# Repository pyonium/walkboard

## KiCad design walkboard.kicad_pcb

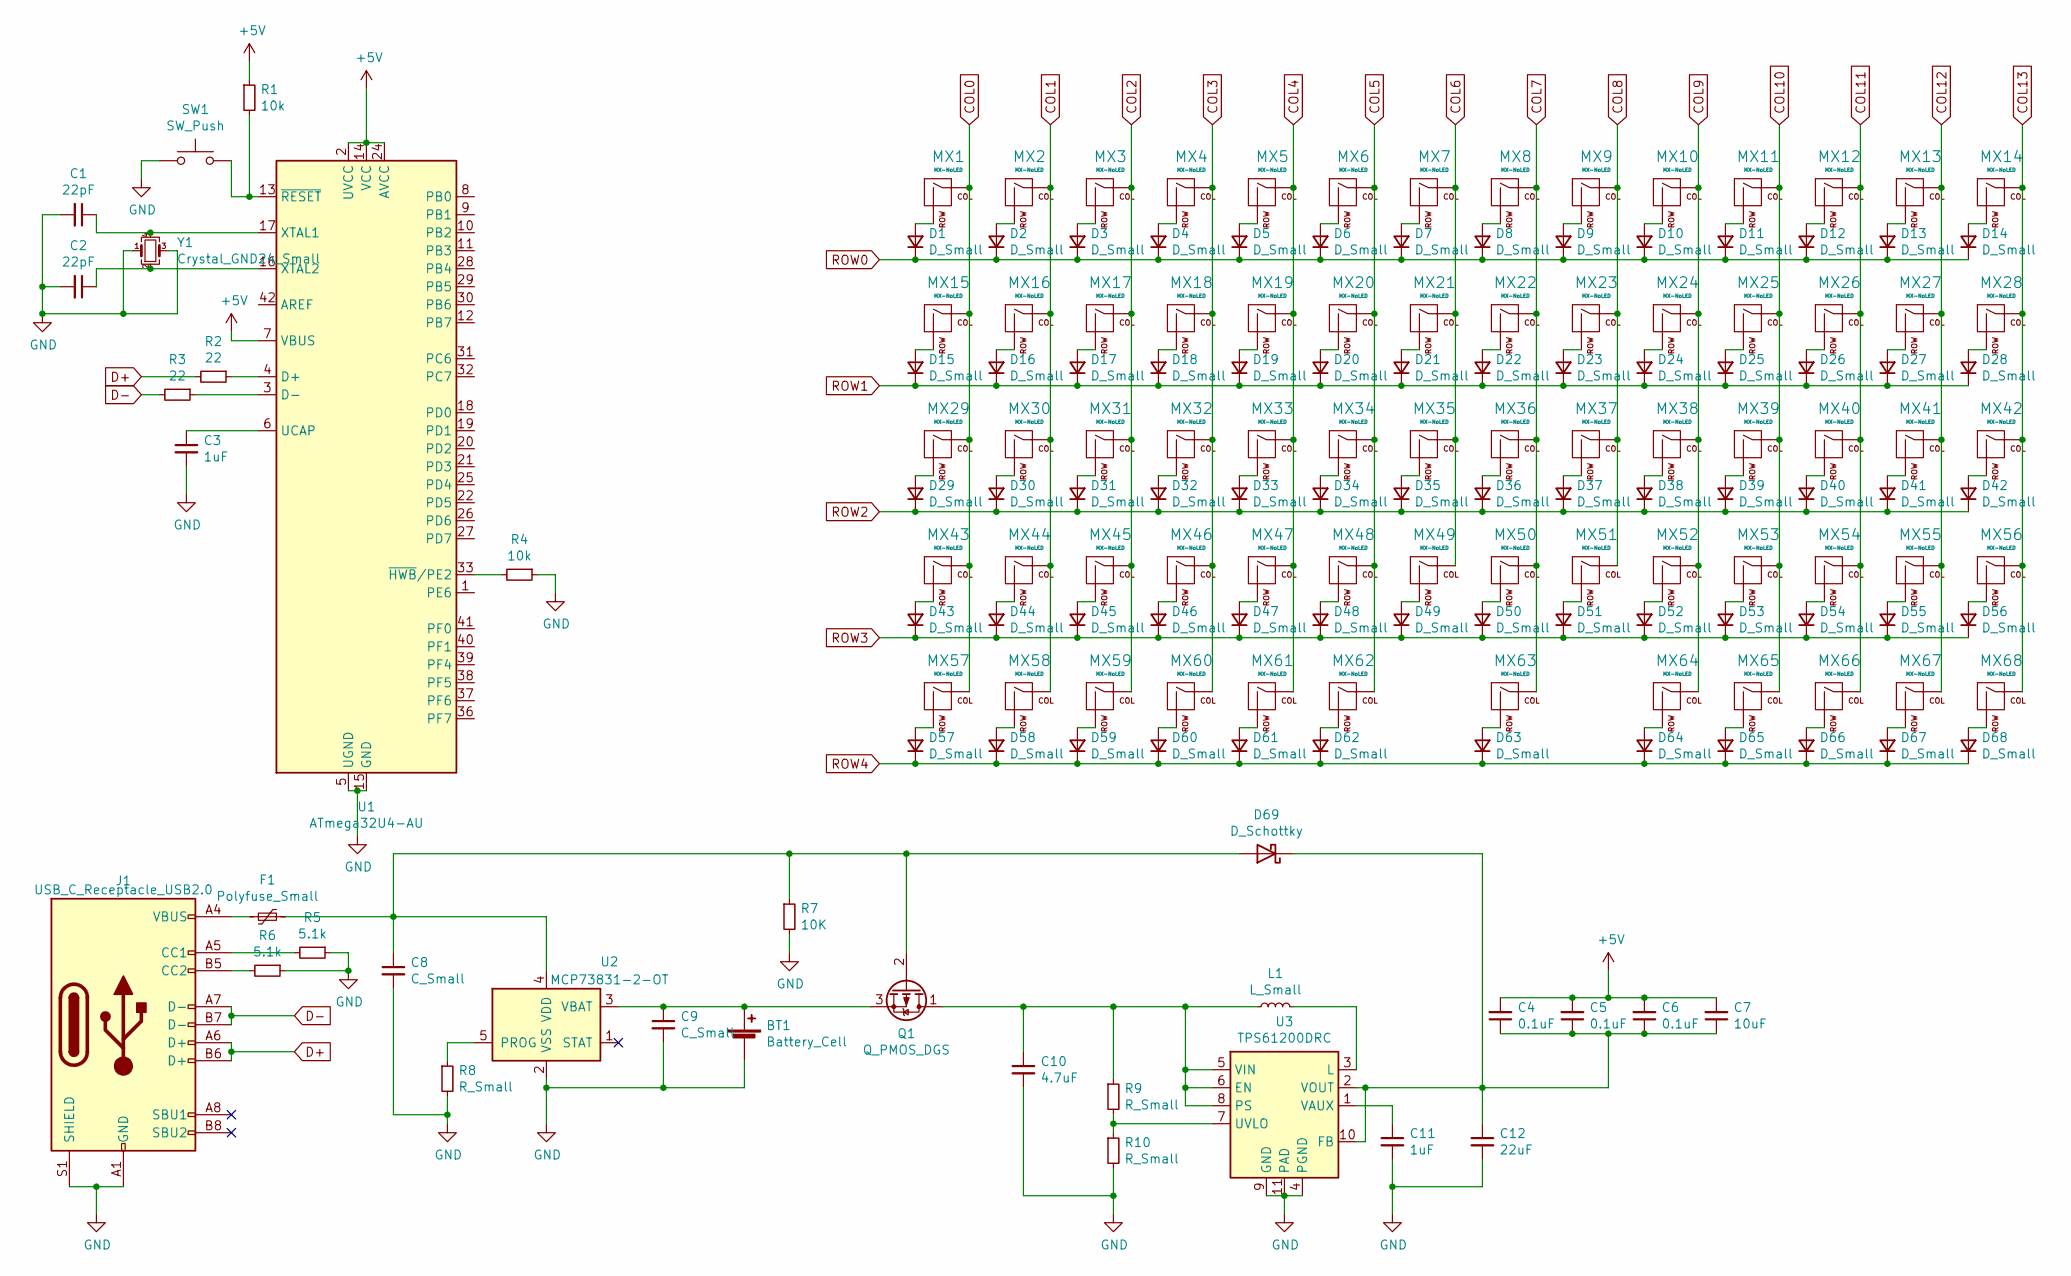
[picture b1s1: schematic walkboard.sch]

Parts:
BT1: Battery_Cell; JST_XH_S2B-XH-A_1x02_P2.50mm_Horizontal
C1, C2: 22pF; C_0805_2012Metric_Pad1.15x1.40mm_HandSolder
C3, C11: 1uF; C_0805_2012Metric_Pad1.15x1.40mm_HandSolder
C4, C5, C6: 0.1uF; C_0805_2012Metric_Pad1.15x1.40mm_HandSolder
C7: 10uF; C_0805_2012Metric_Pad1.15x1.40mm_HandSolder
C8, C9: C_Small; C_0805_2012Metric_Pad1.15x1.40mm_HandSolder
C10: 4.7uF; C_0805_2012Metric_Pad1.15x1.40mm_HandSolder
C12: 22uF; C_0805_2012Metric_Pad1.15x1.40mm_HandSolder
D1, D2, D3, D4, D5, D6, D7, D8, D9, D10, D11, D12, D13, D14, D15, D16, D17, D18, D19, D20, D21, D22, D23, D24, D25, D26, D27, D28, D29, D30, D31, D32, D33, D34, D35, D36, D37, D38, D39, D40, D41, D42, D43, D44, D45, D46, D47, D48, D49, D50, D51, D52, D53, D54, D55, D56, D57, D58, D59, D60, D61, D62, D63, D64, D65, D66, D67, D68: D_Small; D_SOD-123
D69: D_Schottky; D_SOD-123
F1: Polyfuse_Small; Fuse_1206_3216Metric_Pad1.42x1.75mm_HandSolder
J1: USB_C_Receptacle_USB2.0; USB_C_Receptacle_HRO_TYPE-C-31-M-12
L1: L_Small; L_0805_2012Metric_Pad1.15x1.40mm_HandSolder
MX1, MX2, MX3, MX4, MX5, MX6, MX7, MX8, MX9, MX10, MX11, MX12, MX13, MX14, MX15, MX16, MX17, MX18, MX19, MX20, MX21, MX22, MX23, MX24, MX25, MX26, MX27, MX28, MX29, MX30, MX31, MX32, MX33, MX34, MX35, MX36, MX37, MX38, MX39, MX40, MX41, MX42, MX43, MX44, MX45, MX46, MX47, MX48, MX49, MX50, MX51, MX52, MX53, MX54, MX55, MX56, MX57, MX58, MX59, MX60, MX61, MX62, MX63, MX64, MX65, MX66, MX67, MX68: MX-NoLED; Kailh_socket_MX
Q1: Q_PMOS_DGS; SOT-23
R1, R4: 10k; R_0805_2012Metric_Pad1.15x1.40mm_HandSolder
R2, R3: 22; R_0805_2012Metric_Pad1.15x1.40mm_HandSolder
R5, R6: 5.1k; R_0805_2012Metric_Pad1.15x1.40mm_HandSolder
R7: 10K; R_0805_2012Metric_Pad1.15x1.40mm_HandSolder
R8, R9, R10: R_Small; R_0805_2012Metric_Pad1.15x1.40mm_HandSolder
SW1: SW_Push; SKQG-1155865
U1: ATmega32U4-AU; TQFP-44_10x10mm_P0.8mm
U2: MCP73831-2-OT; SOT-23-5
U3: TPS61200DRC; Texas_S-PVSON-N10_ThermalVias
Y1: Crystal_GND24_Small; Crystal_SMD_3225-4Pin_3.2x2.5mm

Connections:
+5V: C4.2, C5.2, C6.2, C7.2, R1.1, U1.2 (UVCC), U1.7 (VBUS), U1.14 (VCC), U1.24 (AVCC), U1.34 (VCC), U1.44 (AVCC)
COL0: MX1.1 (COL), MX15.1 (COL), MX29.1 (COL), MX43.1 (COL), MX57.1 (COL)
COL1: MX2.1 (COL), MX16.1 (COL), MX30.1 (COL), MX44.1 (COL), MX58.1 (COL)
COL2: MX3.1 (COL), MX17.1 (COL), MX31.1 (COL), MX45.1 (COL), MX59.1 (COL)
COL3: MX4.1 (COL), MX18.1 (COL), MX32.1 (COL), MX46.1 (COL), MX60.1 (COL)
COL4: MX5.1 (COL), MX19.1 (COL), MX33.1 (COL), MX47.1 (COL), MX61.1 (COL)
COL5: MX6.1 (COL), MX20.1 (COL), MX34.1 (COL), MX48.1 (COL), MX62.1 (COL)
COL6: MX7.1 (COL), MX21.1 (COL), MX35.1 (COL), MX49.1 (COL)
COL7: MX8.1 (COL), MX22.1 (COL), MX36.1 (COL), MX50.1 (COL), MX63.1 (COL)
COL8: MX9.1 (COL), MX23.1 (COL), MX37.1 (COL), MX51.1 (COL)
COL9: MX10.1 (COL), MX24.1 (COL), MX38.1 (COL), MX52.1 (COL), MX64.1 (COL)
COL10: MX11.1 (COL), MX25.1 (COL), MX39.1 (COL), MX53.1 (COL), MX65.1 (COL)
COL11: MX12.1 (COL), MX26.1 (COL), MX40.1 (COL), MX54.1 (COL), MX66.1 (COL)
COL12: MX13.1 (COL), MX27.1 (COL), MX41.1 (COL), MX55.1 (COL), MX67.1 (COL)
COL13: MX14.1 (COL), MX28.1 (COL), MX42.1 (COL), MX56.1 (COL), MX68.1 (COL)
D+: J1.A6 (D+), J1.B6 (D+), R2.2
D-: J1.A7 (D-), J1.B7 (D-), R3.2
GND: BT1.2 (-), C1.2, C2.2, C3.2, C8.2, C9.2, C10.2, C11.2, C12.2, J1.A1 (GND), J1.A12 (GND), J1.B1 (GND), J1.B12 (GND), J1.S1 (SHIELD), R4.1, R5.1, R6.1, R7.2, R8.2, R10.2, SW1.1, U1.5 (UGND), U1.15 (GND), U1.23 (GND), U1.35 (GND), U1.43 (GND), U2.2 (VSS), U3.4 (PGND), U3.9 (GND), U3.11 (PAD), Y1.1, Y1.3
unnamed: BT1.1 (+), C9.1, Q1.3 (S), U2.3 (VBAT)
unnamed: C1.1, U1.17 (XTAL1), Y1.4
unnamed: C2.1, U1.16 (XTAL2), Y1.2
unnamed: C3.1, U1.6 (UCAP)
unnamed: C8.1, D69.2 (A), F1.2, Q1.2 (G), R7.1, U2.4 (VDD)
unnamed: C10.1, L1.1, Q1.1 (D), R9.1, U3.5 (VIN), U3.6 (EN), U3.8 (PS)
unnamed: C11.1, U3.1 (VAUX)
unnamed: C4.1, C5.1, C6.1, C7.1, C12.1, D69.1 (K), U3.2 (VOUT), U3.10 (FB)
unnamed: D1.2 (A), MX1.2 (ROW)
unnamed: D2.2 (A), MX2.2 (ROW)
unnamed: D3.2 (A), MX3.2 (ROW)
unnamed: D4.2 (A), MX4.2 (ROW)
unnamed: D5.2 (A), MX5.2 (ROW)
unnamed: D6.2 (A), MX6.2 (ROW)
unnamed: D7.2 (A), MX7.2 (ROW)
unnamed: D8.2 (A), MX8.2 (ROW)
unnamed: D9.2 (A), MX9.2 (ROW)
unnamed: D10.2 (A), MX10.2 (ROW)
unnamed: D11.2 (A), MX11.2 (ROW)
unnamed: D12.2 (A), MX12.2 (ROW)
unnamed: D13.2 (A), MX13.2 (ROW)
unnamed: D14.2 (A), MX14.2 (ROW)
unnamed: D15.2 (A), MX15.2 (ROW)
unnamed: D16.2 (A), MX16.2 (ROW)
unnamed: D17.2 (A), MX17.2 (ROW)
unnamed: D18.2 (A), MX18.2 (ROW)
unnamed: D19.2 (A), MX19.2 (ROW)
unnamed: D20.2 (A), MX20.2 (ROW)
unnamed: D21.2 (A), MX21.2 (ROW)
unnamed: D22.2 (A), MX22.2 (ROW)
unnamed: D23.2 (A), MX23.2 (ROW)
unnamed: D24.2 (A), MX24.2 (ROW)
unnamed: D25.2 (A), MX25.2 (ROW)
unnamed: D26.2 (A), MX26.2 (ROW)
unnamed: D27.2 (A), MX27.2 (ROW)
unnamed: D28.2 (A), MX28.2 (ROW)
unnamed: D29.2 (A), MX29.2 (ROW)
unnamed: D30.2 (A), MX30.2 (ROW)
unnamed: D31.2 (A), MX31.2 (ROW)
unnamed: D32.2 (A), MX32.2 (ROW)
unnamed: D33.2 (A), MX33.2 (ROW)
unnamed: D34.2 (A), MX34.2 (ROW)
unnamed: D35.2 (A), MX35.2 (ROW)
unnamed: D36.2 (A), MX36.2 (ROW)
unnamed: D37.2 (A), MX37.2 (ROW)
unnamed: D38.2 (A), MX38.2 (ROW)
unnamed: D39.2 (A), MX39.2 (ROW)
unnamed: D40.2 (A), MX40.2 (ROW)
unnamed: D41.2 (A), MX41.2 (ROW)
unnamed: D42.2 (A), MX42.2 (ROW)
unnamed: D43.2 (A), MX43.2 (ROW)
unnamed: D44.2 (A), MX44.2 (ROW)
unnamed: D45.2 (A), MX45.2 (ROW)
unnamed: D46.2 (A), MX46.2 (ROW)
unnamed: D47.2 (A), MX47.2 (ROW)
unnamed: D48.2 (A), MX48.2 (ROW)
unnamed: D49.2 (A), MX49.2 (ROW)
unnamed: D50.2 (A), MX50.2 (ROW)
unnamed: D51.2 (A), MX51.2 (ROW)
unnamed: D52.2 (A), MX52.2 (ROW)
unnamed: D53.2 (A), MX53.2 (ROW)
unnamed: D54.2 (A), MX54.2 (ROW)
unnamed: D55.2 (A), MX55.2 (ROW)
unnamed: D56.2 (A), MX56.2 (ROW)
unnamed: D57.2 (A), MX57.2 (ROW)
unnamed: D58.2 (A), MX58.2 (ROW)
unnamed: D59.2 (A), MX59.2 (ROW)
unnamed: D60.2 (A), MX60.2 (ROW)
unnamed: D61.2 (A), MX61.2 (ROW)
unnamed: D62.2 (A), MX62.2 (ROW)
unnamed: D63.2 (A), MX63.2 (ROW)
unnamed: D64.2 (A), MX64.2 (ROW)
unnamed: D65.2 (A), MX65.2 (ROW)
unnamed: D66.2 (A), MX66.2 (ROW)
unnamed: D67.2 (A), MX67.2 (ROW)
unnamed: D68.2 (A), MX68.2 (ROW)
unnamed: F1.1, J1.A4 (VBUS), J1.A9 (VBUS), J1.B4 (VBUS), J1.B9 (VBUS)
unnamed: J1.A5 (CC1), R5.2
unnamed: J1.B5 (CC2), R6.2
unnamed: L1.2, U3.3 (L)
unnamed: R1.2, SW1.2, U1.13 (~RESET)
unnamed: R2.1, U1.4 (D+)
unnamed: R3.1, U1.3 (D-)
unnamed: R4.2, U1.33 (~HWB~/PE2)
unnamed: R8.1, U2.5 (PROG)
unnamed: R9.2, R10.1, U3.7 (UVLO)
ROW0: D1.1 (K), D2.1 (K), D3.1 (K), D4.1 (K), D5.1 (K), D6.1 (K), D7.1 (K), D8.1 (K), D9.1 (K), D10.1 (K), D11.1 (K), D12.1 (K), D13.1 (K), D14.1 (K)
ROW1: D15.1 (K), D16.1 (K), D17.1 (K), D18.1 (K), D19.1 (K), D20.1 (K), D21.1 (K), D22.1 (K), D23.1 (K), D24.1 (K), D25.1 (K), D26.1 (K), D27.1 (K), D28.1 (K)
ROW2: D29.1 (K), D30.1 (K), D31.1 (K), D32.1 (K), D33.1 (K), D34.1 (K), D35.1 (K), D36.1 (K), D37.1 (K), D38.1 (K), D39.1 (K), D40.1 (K), D41.1 (K), D42.1 (K)
ROW3: D43.1 (K), D44.1 (K), D45.1 (K), D46.1 (K), D47.1 (K), D48.1 (K), D49.1 (K), D50.1 (K), D51.1 (K), D52.1 (K), D53.1 (K), D54.1 (K), D55.1 (K), D56.1 (K)
ROW4: D57.1 (K), D58.1 (K), D59.1 (K), D60.1 (K), D61.1 (K), D62.1 (K), D63.1 (K), D64.1 (K), D65.1 (K), D66.1 (K), D67.1 (K), D68.1 (K)

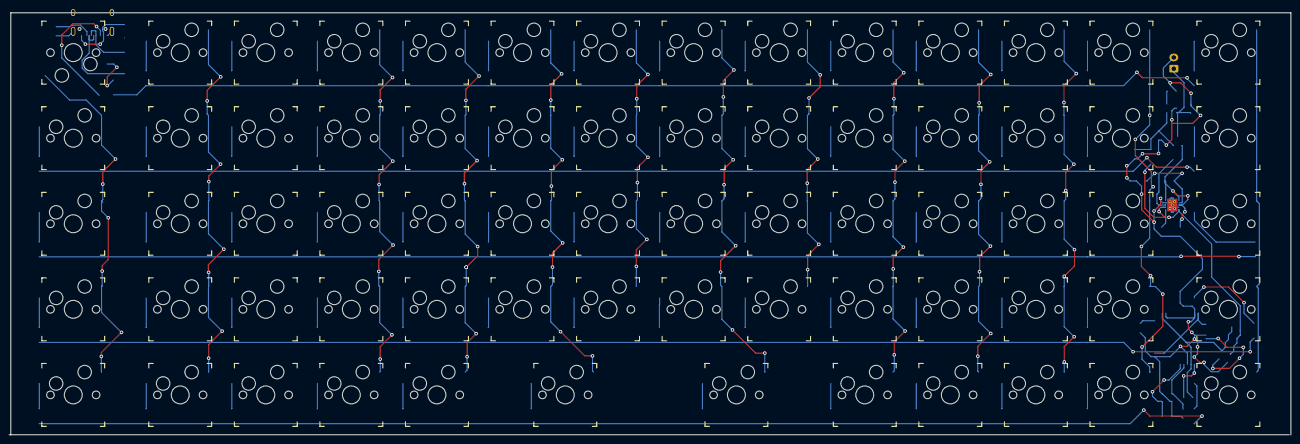
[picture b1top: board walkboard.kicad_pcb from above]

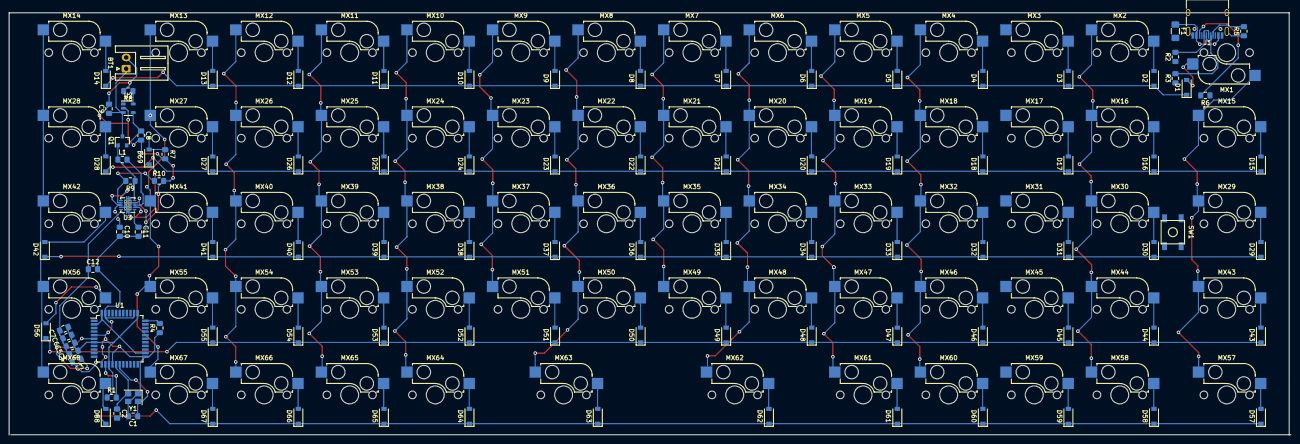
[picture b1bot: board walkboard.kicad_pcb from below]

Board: 2 copper layers, 285.4 x 94.0 mm, 169 parts (101 on the bottom side), 109 nets.

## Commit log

2020-08-04 initialised kicad project
2020-08-04 added submodules
2020-08-04 added parts
2020-08-04 followed tutorial some more
2020-08-04 finished microcontroller
2020-08-04 added submodule for kaihl
2020-08-04 started work on pcb
2020-08-05 fixed
2020-08-05 added stuff
